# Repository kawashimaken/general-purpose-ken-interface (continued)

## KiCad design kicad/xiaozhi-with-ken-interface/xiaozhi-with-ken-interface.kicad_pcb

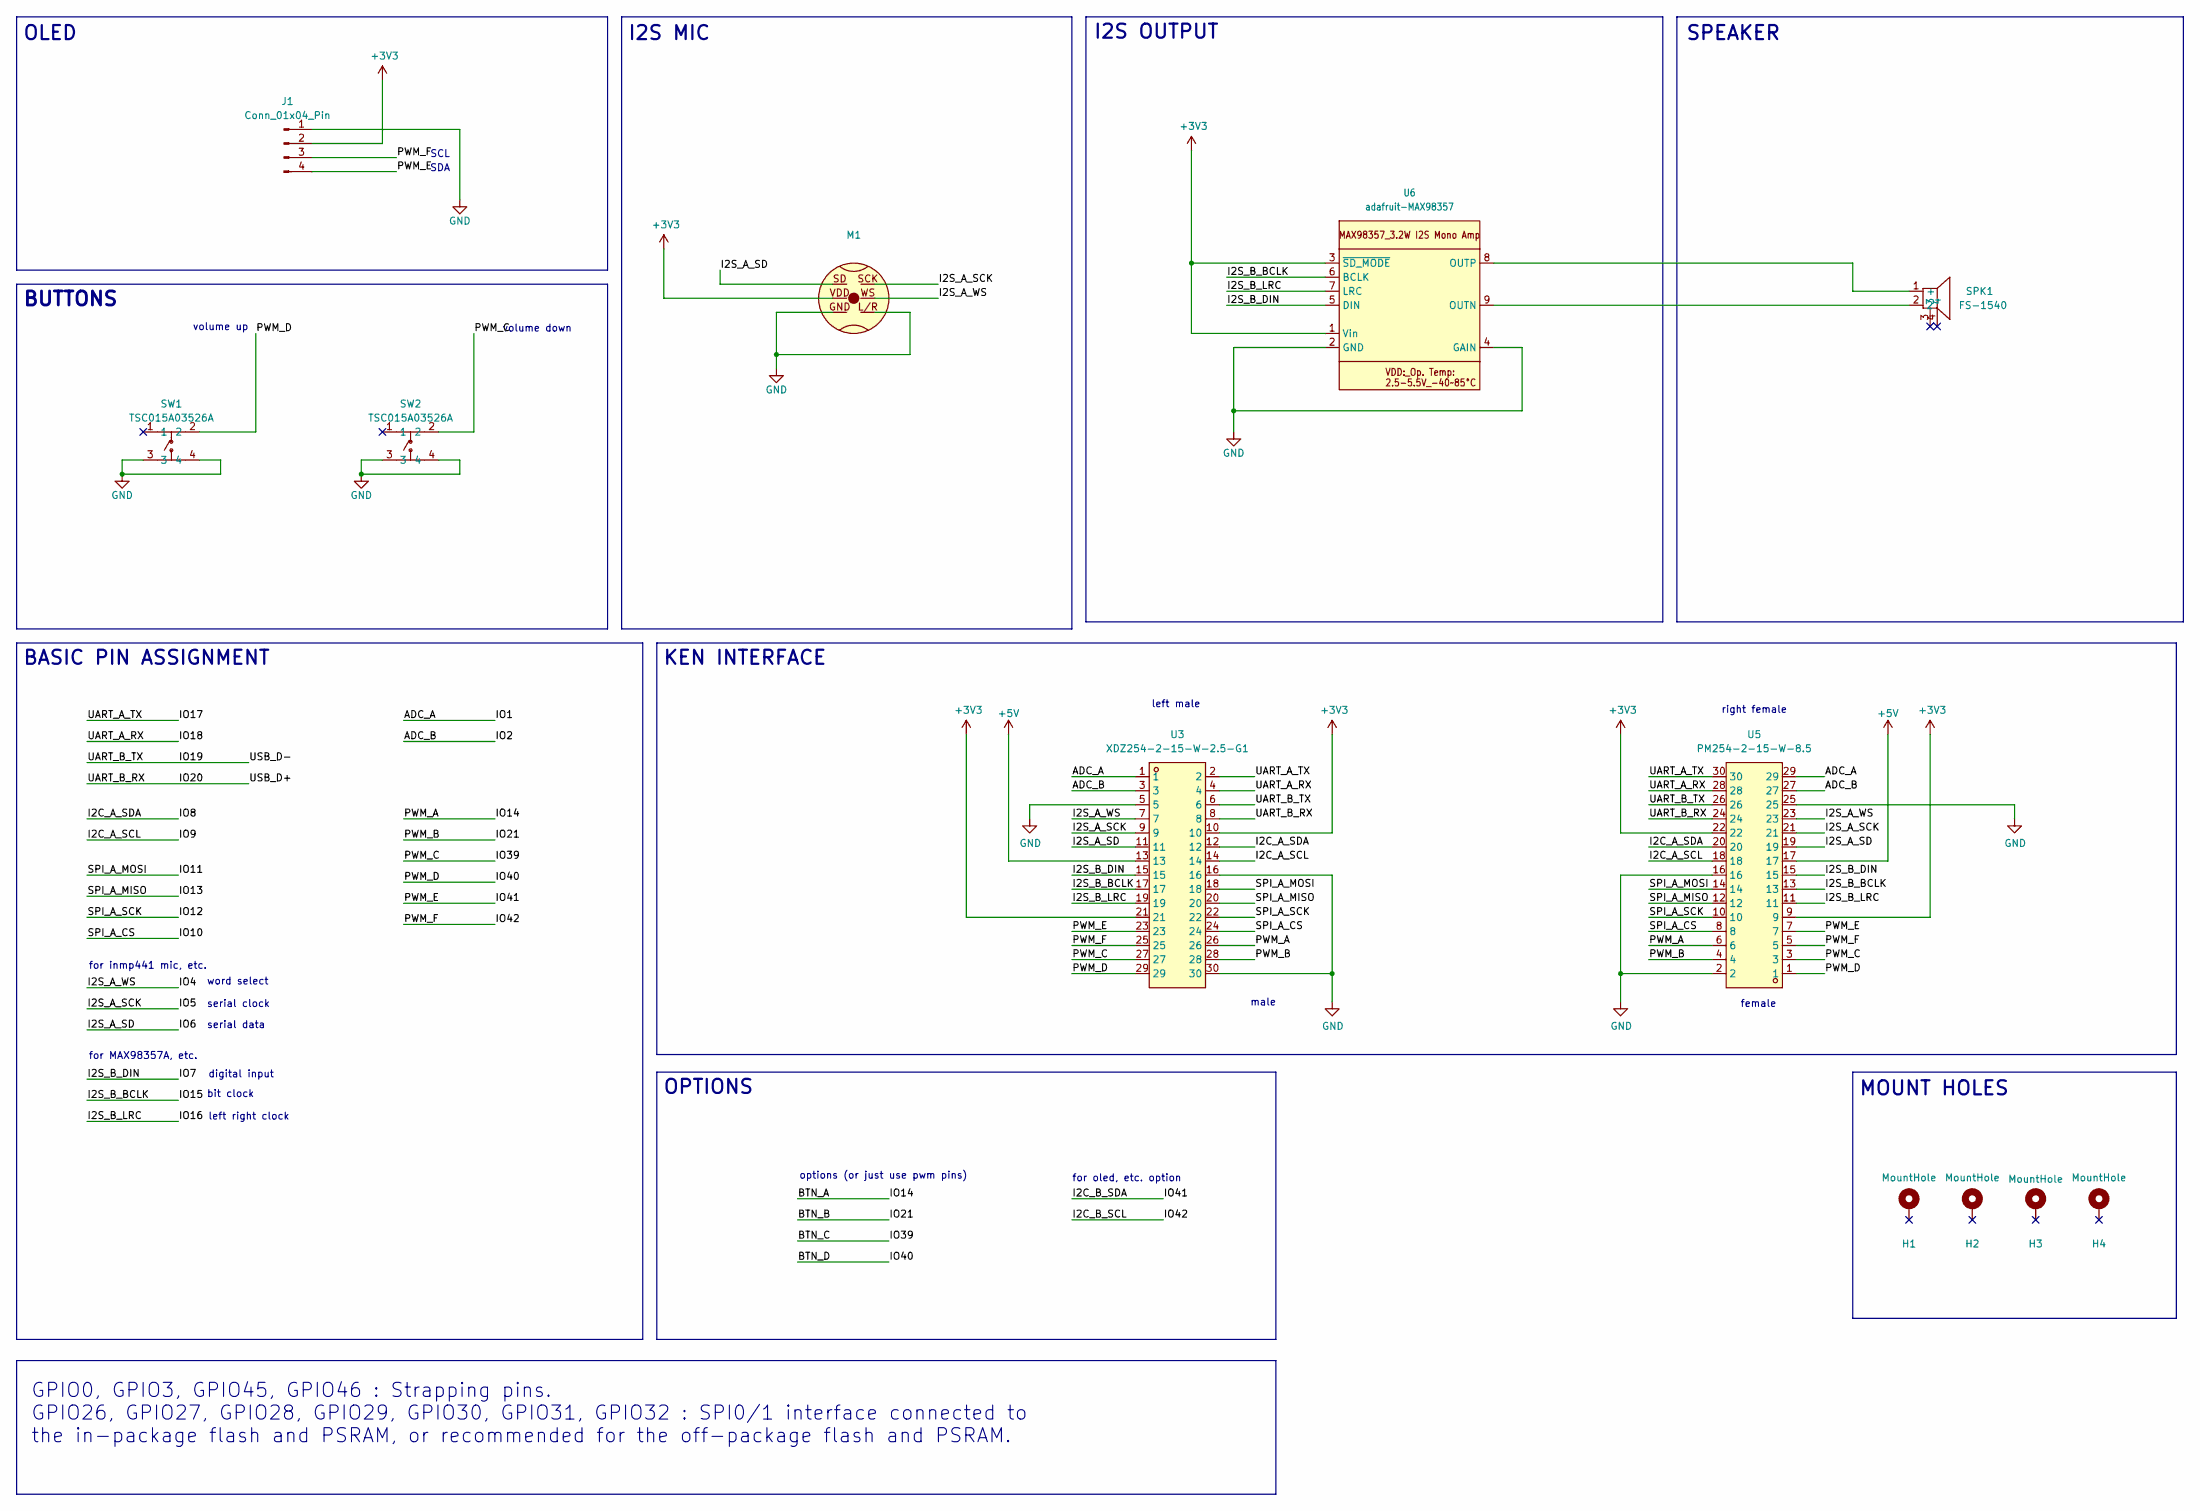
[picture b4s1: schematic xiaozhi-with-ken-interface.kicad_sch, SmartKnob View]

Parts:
H1, H2, H3, H4: MountHole; MountingHole_3.2mm_M3_DIN965_Pad; LCSC C2911210 or C2911532 (screw), C2961595 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
J1: Conn_01x04_Pin; SSD1306-0.91-OLED-4pin-128x32
M1: INMP441_OMNIDIRECTIONAL_MICROPHONE_MODULE
SPK1: FS-1540; BUZ-SMD_5P-L15.0-W15.0-P13.7-BL; LCSC Part C482341
SW1, SW2: TSC015A03526A; SW-SMD_4P-L4.5-W4.5-P3.00-LS6.8; LCSC Part C2888900
U3: XDZ254-2-15-W-2.5-G1; HDR-TH_30P-P2.54-H-M-R2-C15-S2.54-N; LCSC Part C18905913
U5: PM254-2-15-W-8.5; HDR-TH_30P-P2.54-H-F-R2-C15-W8.5; LCSC Part C2897435
U6: adafruit-MAX98357

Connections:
+3V3: J1.2, M1.VDD, U3.10, U3.21, U5.9, U5.22, U6.1 (Vin), U6.3 (~SD_MODE)
+5V: U3.13, U5.17
/ADC_A: U3.1, U5.29
/ADC_B: U3.3, U5.27
/BTN_A: U3.26, U5.6
/BTN_B: U3.28, U5.4
/BTN_C: SW2.2, U3.27, U5.3
/BTN_D: SW1.2, U3.29, U5.1
/I2C_A_SCL: U3.14, U5.18
/I2C_A_SDA: U3.12, U5.20
/I2C_B_SCL: J1.3, U3.25, U5.5
/I2C_B_SDA: J1.4, U3.23, U5.7
/I2S_A_SCK: M1.SCK, U3.9, U5.21
/I2S_A_SD: M1.SD, U3.11, U5.19
/I2S_A_WS: M1.WS, U3.7, U5.23
/I2S_B_BCLK: U3.17, U5.13, U6.6 (BCLK)
/I2S_B_DIN: U3.15, U5.15, U6.5 (DIN)
/I2S_B_LRC: U3.19, U5.11, U6.7 (LRC)
/IO10: U3.24, U5.8
/IO11: U3.18, U5.14
/IO12: U3.22, U5.10
/IO13: U3.20, U5.12
/IO17: U3.2, U5.30
/IO18: U3.4, U5.28
/IO19: U3.6, U5.26
/IO20: U3.8, U5.24
GND: J1.1, M1.GND, M1.L/R, SW1.3, SW1.4, SW2.3, SW2.4, U3.5, U3.16, U3.30, U5.2, U5.16, U5.25, U6.2 (GND), U6.4 (GAIN)
unnamed: SPK1.1 (+), U6.8 (OUTP)
unnamed: SPK1.2, U6.9 (OUTN)

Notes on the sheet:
OLED
for MAX98357A, etc.
KEN INTERFACE
GPIO0, GPIO3, GPIO45, GPIO46 : Strapping pins. GPIO26, GPIO27, GPIO28, GPIO29, GPIO30, GPIO31, GPIO32 : SPI0/1 interface connected to the in-package flash and PSRAM, or recommended for the off-package flash and PSRAM.
MOUNT HOLES
right female
SDA
female
word select
BASIC PIN ASSIGNMENT
male
serial clock
volume down
SPEAKER
left right clock
bit clock
left male
I2S MIC
OPTIONS
BUTTONS
options (or just use pwm pins)
volume up
SCL
digital input
serial data
I2S OUTPUT
for oled, etc. option
for inmp441 mic, etc.

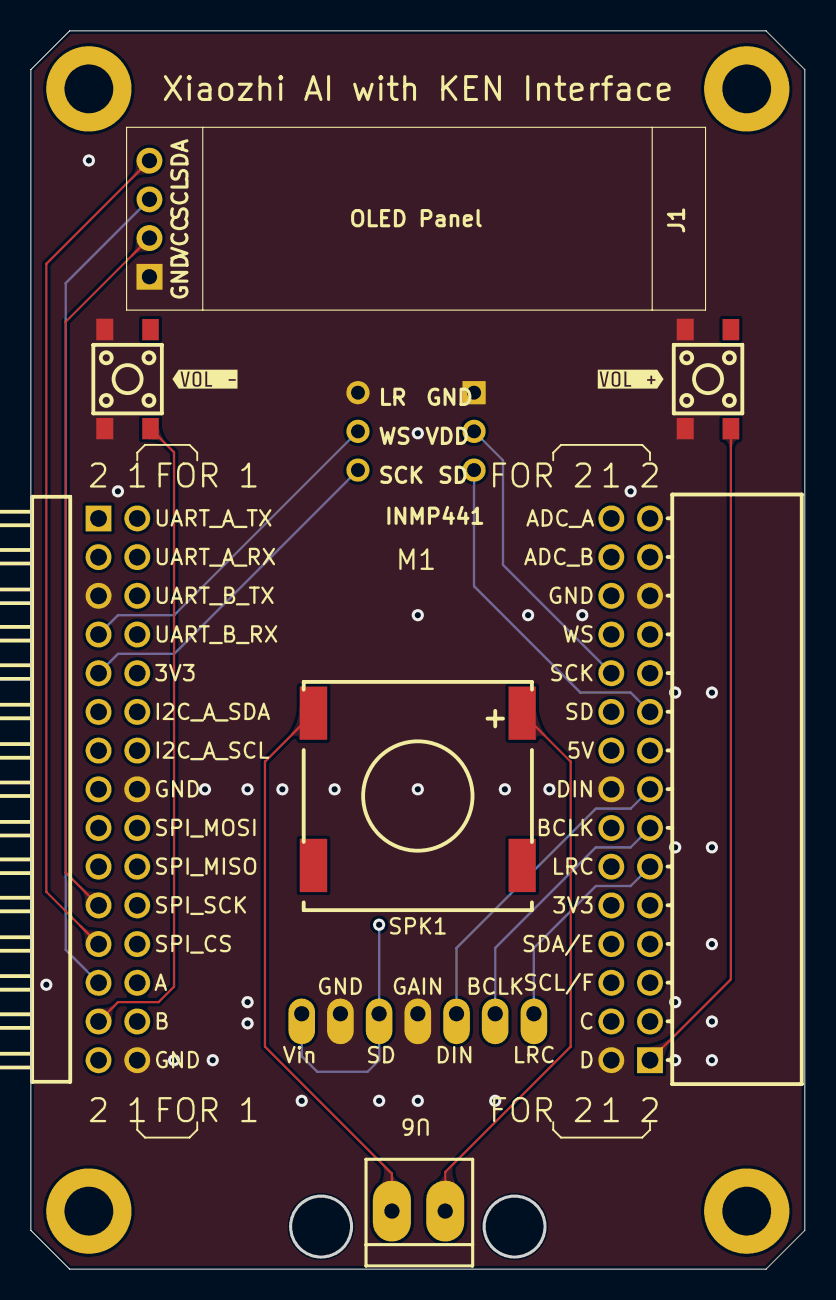
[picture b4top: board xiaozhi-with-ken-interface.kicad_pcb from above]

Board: 4 copper layers, 50.8 x 81.3 mm, 14 parts (0 on the bottom side), 29 nets.

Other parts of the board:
kibuzzard-69756C5B: G***; kibuzzard-69756C5B
kibuzzard-69756C68: G***; kibuzzard-69756C68

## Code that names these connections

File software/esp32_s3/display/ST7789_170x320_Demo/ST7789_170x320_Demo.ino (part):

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 * Library : LovyanGFX (latest)
 *
 * Pin Assignments
 *  MOSI  GPIO11
 *  SCK   GPIO12
 *  MISO  GPIO13  (connected but unused)
 *  CS    GPIO10
 *  DC    GPIO17
 *  RESET GPIO18
 *  BL    tie to 3.3V
 */

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
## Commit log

2026-01-20 get parts ready, first routing
2026-01-20 fix left pin header pin assignment
2026-01-20 adjust traces
2026-01-21 add pin label, adjust routing, add PWM pins
2026-01-22 add protect diode, improve trace routing, add vias, add user button and user led, improve schematic, add texts
2026-01-23 improve schematic and trace routing, improve silk text, etc
2026-01-23 a little update for layouts and routing
2026-01-23 rename ADC_1 to ADC_A, ADC_2 to ADC_B,also update the silk text
2026-01-23 update schematic
2026-01-24 add KiCad project for xiaozhi AI with KEN interface
2026-01-24 update s3 model for oled display
2026-01-25 improve routing for ESP32-S3 board
2026-01-25 add boot button to ESP32-S3 board, add speaker to xiaozhi, improve xiaozhi board schematic and routing.
2026-01-25 small update
2026-01-25 adjust 3d model position
2026-01-25 final adjust, send to pcb maker
2026-02-02 add template project
2026-02-02 add text
2026-02-02 add Raspberry Pi Pico with KEN interface, WIP
2026-02-02 edited labels for template project PCB
2026-02-03 bring back button symbol and foot print, did some routing.
2026-02-03 first routing for pico
2026-02-03 add button and LED
2026-02-04 finalize pin assignment for pico board
2026-02-04 trace adjust
2026-02-05 add display board with ken interface
2026-02-11 ready to send pico board to manufacturing
2026-02-19 add 3d models for display, adjust pin header placement
2026-02-23 fix text
2026-02-24 display board is ready to send to pcb maker
2026-02-24 add teartrop
2026-03-02 add user led demo code
2026-03-04 sda:14, scl:15 I2C oled display demo, and mic wave form demo
2026-03-07 fix labels, update manufacture files
2026-03-08 add demo codes for displays
2026-03-12 use 4,5 for default I2C pins
2026-03-12 add labels for pico pins
2026-03-15 adjust labels, send to pcb maker
2026-03-19 add reset button
2026-03-26 update symbol
2026-03-27 save kicad file
2026-04-12 update pico 3d model size
2026-04-17 add gitignore files
2026-04-21 add project for renewed display board
2026-04-22 new display board send to pcb maker
2026-04-27 add capacitor
2026-05-04 Revise README with KEN Interface details
    Updated project name and added detailed description of KEN Interface, its features, and hardware specifications.
2026-05-04 update to new display board pin assignment
2026-05-06 Update YouTube links and descriptions in README
